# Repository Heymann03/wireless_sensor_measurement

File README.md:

# master research project
## Design and Realization of Wireless Measurement System for Resistive Sensors
### Objectives
1. Measuring the resistance of a sensor of any given range from 200K - 6M.
2. Displaying the data through an OLED.
3. Transmitting the acquired data to a remote station.
4. Monitoring the resistance in real-time.
5. Recording the measured data.

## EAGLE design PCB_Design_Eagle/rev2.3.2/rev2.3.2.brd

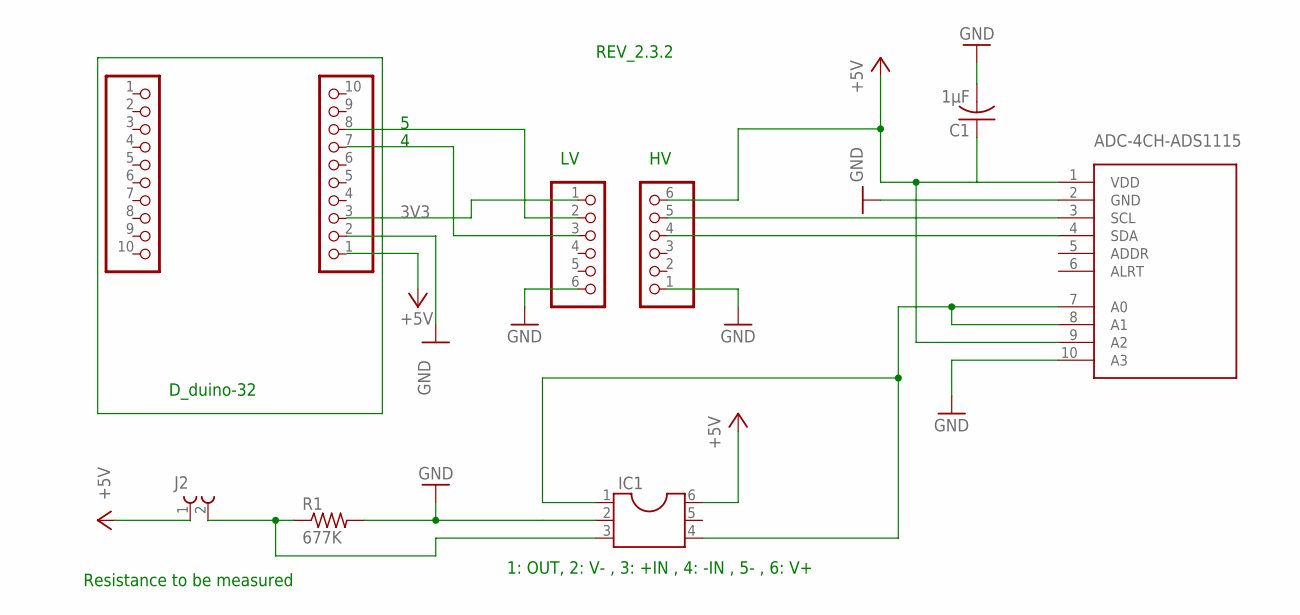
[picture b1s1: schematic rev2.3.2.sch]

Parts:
C1: 1µF; C025-025X050
IC1: DIL6S; SOCKET-06
J2: 691103110002
JP1, JP4: PINHD-1X6; 1X06
JP3, JP5: PINHD-1X10; 1X10
R1: 677K; 0204/5
U$1: ADC-4CH-ADS1115

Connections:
3V3: JP1.1
4: JP1.3
+5V: IC1.6, J2.1
A1: IC1.1, IC1.4, U$1.7 (A0), U$1.8 (A1)
GND: C1.2, IC1.2, JP1.6, JP4.1, JP5.2, R1.2, U$1.2 (GND), U$1.10 (A3)
unnamed: IC1.3, J2.2, R1.1
unnamed: JP1.2, JP5.8
unnamed: JP4.5, U$1.3 (SCL)
unnamed: JP4.4, U$1.4 (SDA)
VDD: C1.1, JP4.6, U$1.9 (A2)

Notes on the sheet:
Resistance to be measured
1: OUT, 2: V- , 3: +IN , 4: -IN , 5- , 6: V+
D_duino-32
REV_2.3.2

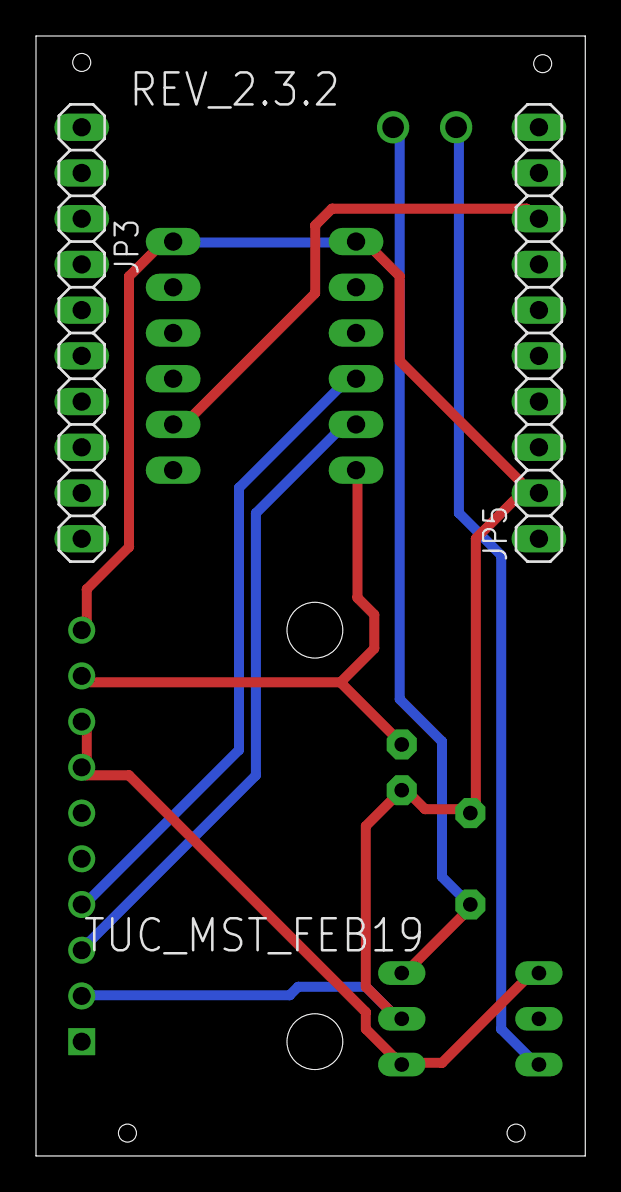
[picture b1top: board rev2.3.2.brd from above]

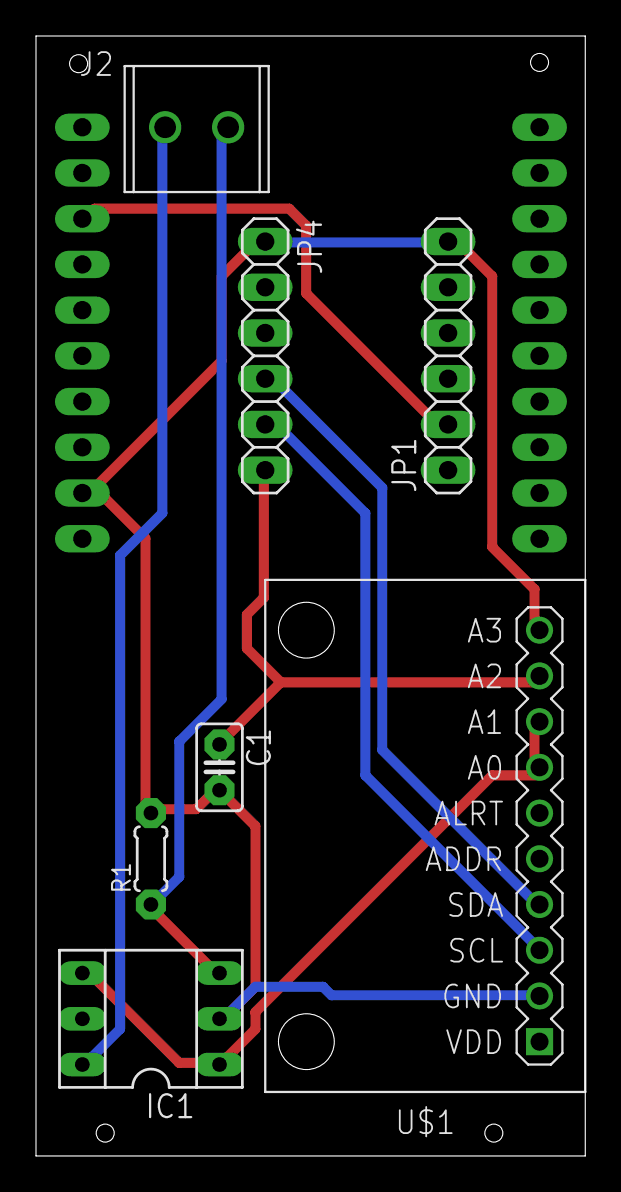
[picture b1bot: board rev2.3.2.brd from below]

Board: 2 copper layers, 30.5 x 62.2 mm, 9 parts (7 on the bottom side), 8 nets.

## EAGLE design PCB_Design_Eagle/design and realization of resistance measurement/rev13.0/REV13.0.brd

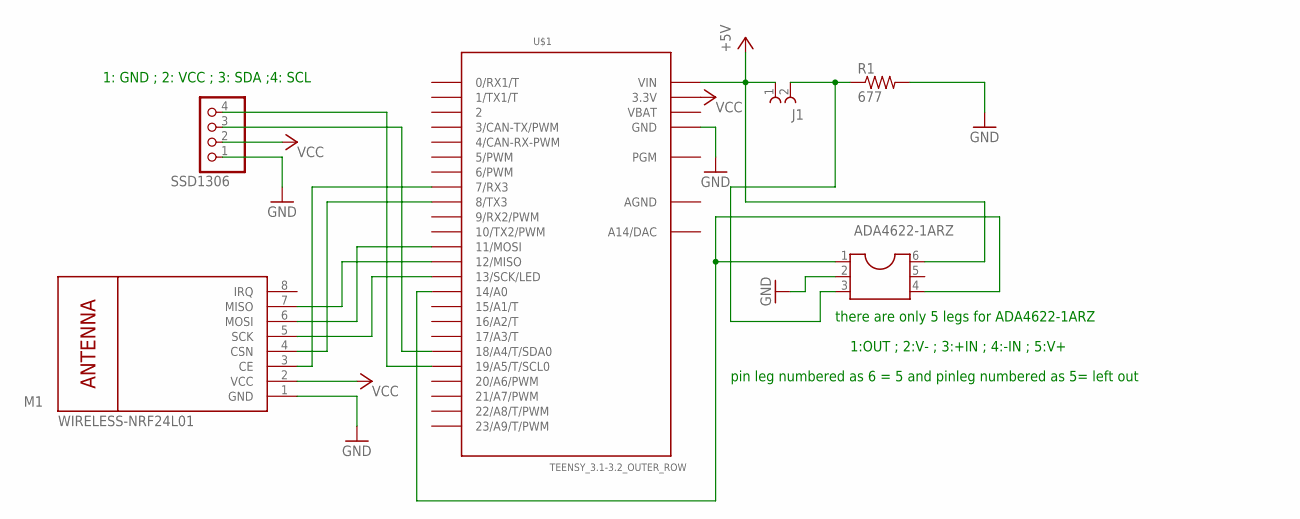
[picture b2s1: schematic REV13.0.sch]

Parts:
ADA4622-1ARZ: DIL6/4; DIL06-4
J1: 691214100002
M1: WIRELESS-NRF24L01
R1: 677; 0204/5
SSD1306: PINHD-1X4; 1X04
U$1: TEENSY_3.1-3.2_OUTER_ROW; TEENSY_3.0-3.2&LC_OUTER_ROW

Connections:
+5V: ADA4622-1ARZ.6, J1.1 (2), U$1.VIN
AGND: U$1.AGND
GND: ADA4622-1ARZ.2, M1.1 (GND), R1.2, SSD1306.1, U$1.GND, U$1.GND1 (GND)
unnamed: ADA4622-1ARZ.3, J1.2 (1), R1.1
unnamed: M1.5 (SCK), U$1.13 (13/SCK/LED)
unnamed: M1.6 (MOSI), U$1.11 (11/MOSI)
unnamed: M1.7 (MISO), U$1.12 (12/MISO)
unnamed: M1.4 (CSN), U$1.8 (8/TX3)
unnamed: M1.3 (CE), U$1.7 (7/RX3)
unnamed: SSD1306.4, U$1.19/A5 (19/A5/T/SCL0)
unnamed: SSD1306.3, U$1.18/A4 (18/A4/T/SDA0)
unnamed: ADA4622-1ARZ.1, ADA4622-1ARZ.4, U$1.14/A0
VBAT: U$1.VBAT
VCC: M1.2 (VCC), SSD1306.2, U$1.3.3V, U$1.3.3V1 (3.3V)

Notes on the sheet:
1: GND ; 2: VCC ; 3: SDA ;4: SCL
1:OUT ; 2:V- ; 3:+IN ; 4:-IN ; 5:V+
pin leg numbered as 6 = 5 and pinleg numbered as 5= left out
there are only 5 legs for ADA4622-1ARZ

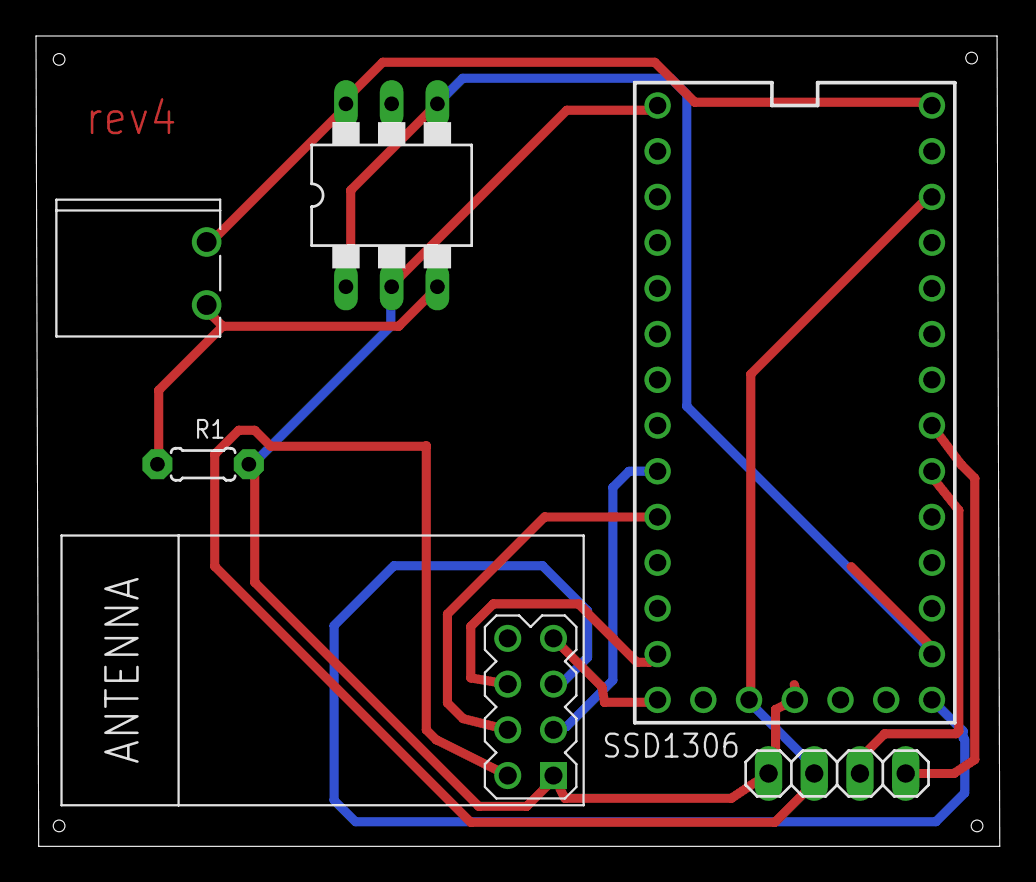
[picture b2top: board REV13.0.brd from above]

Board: 2 copper layers, 53.5 x 45.0 mm, 6 parts (0 on the bottom side), 12 nets.

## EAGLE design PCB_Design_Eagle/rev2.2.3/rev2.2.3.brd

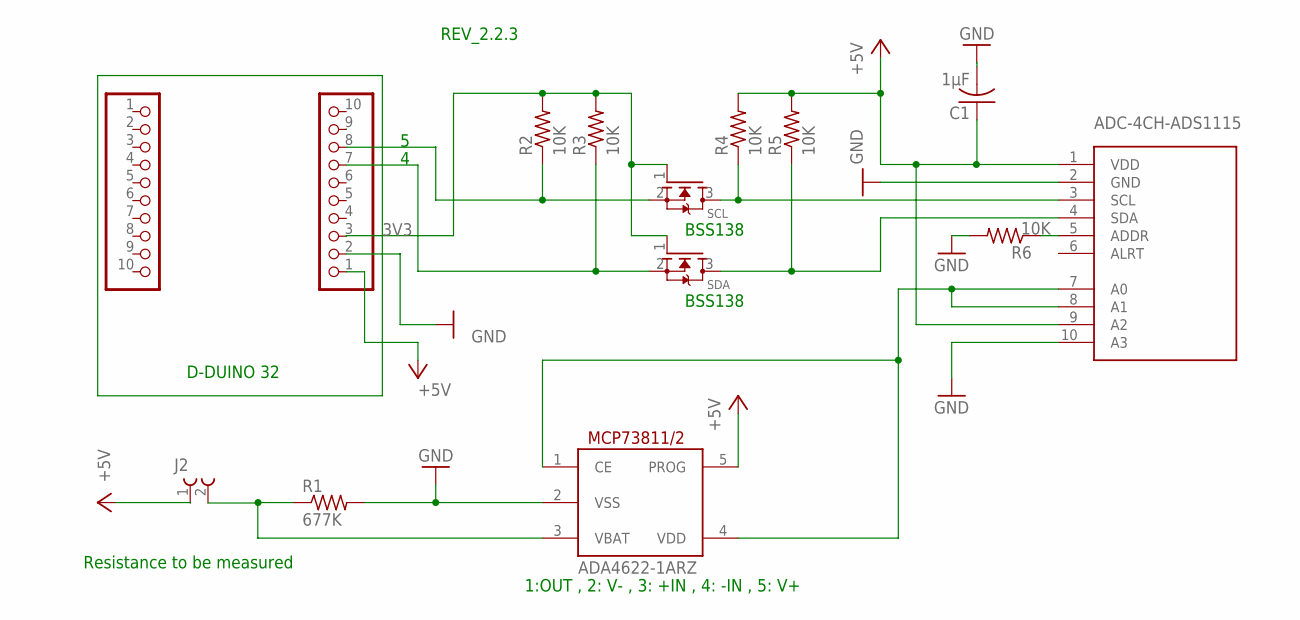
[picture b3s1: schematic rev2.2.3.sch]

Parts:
ADA4622-1ARZ: MCP73811/2; SOT23-5L
C1: 1µF; C1608
J2: 691103110002
JP1, JP3: PINHD-1X10; 1X10
R1: 677K; M0805
R2, R3, R4, R5, R6: 10K; M0805
SCL: MOSFET-NWAVE; SOT23-W
SDA: MOSFET-NWAVE; SOT23-W
U$1: ADC-4CH-ADS1115

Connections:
3V3: JP1.3, R2.2, R3.2, SCL.1 (G), SDA.1 (G)
4: JP1.7, R3.1, SDA.2 (S)
+5V: ADA4622-1ARZ.5 (PROG), J2.1, JP1.1
A1: ADA4622-1ARZ.1 (CE), ADA4622-1ARZ.4 (VDD), U$1.7 (A0), U$1.8 (A1)
GND: ADA4622-1ARZ.2 (VSS), C1.2, JP1.2, R1.2, R6.2, U$1.2 (GND), U$1.10 (A3)
unnamed: ADA4622-1ARZ.3 (VBAT), J2.2, R1.1
unnamed: JP1.8, R2.1, SCL.2 (S)
unnamed: R6.1, U$1.5 (ADDR)
SCL: R4.1, SCL.3 (D), U$1.3 (SCL)
SDA: R5.1, SDA.3 (D), U$1.4 (SDA)
VDD: C1.1, R4.2, R5.2, U$1.1 (VDD), U$1.9 (A2)

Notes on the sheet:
1:OUT , 2: V- , 3: +IN , 4: -IN , 5: V+
Resistance to be measured
BSS138
REV_2.2.3
D-DUINO 32

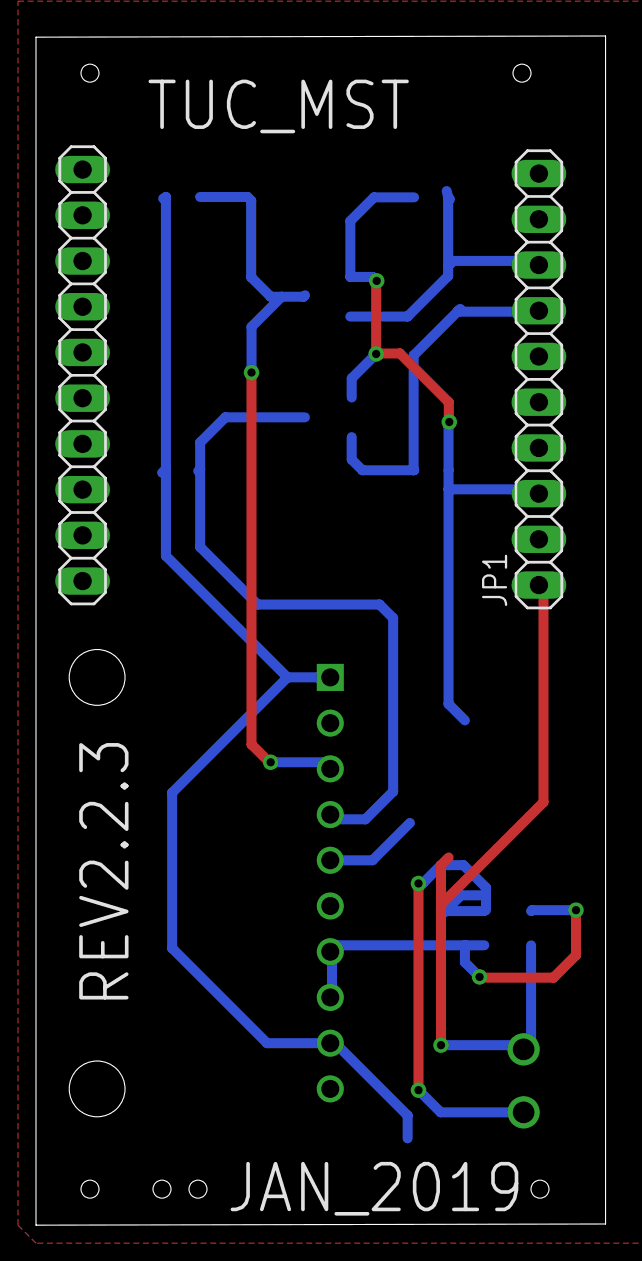
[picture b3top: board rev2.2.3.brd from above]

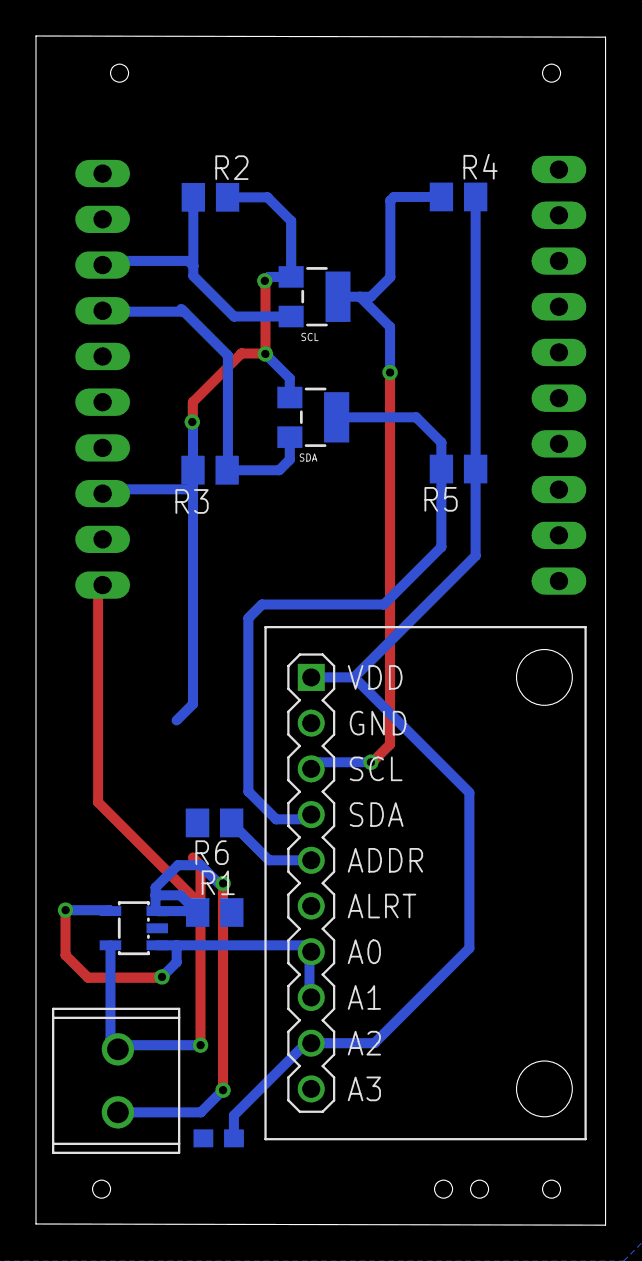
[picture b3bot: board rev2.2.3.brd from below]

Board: 2 copper layers, 31.6 x 66.1 mm, 14 parts (12 on the bottom side), 11 nets.

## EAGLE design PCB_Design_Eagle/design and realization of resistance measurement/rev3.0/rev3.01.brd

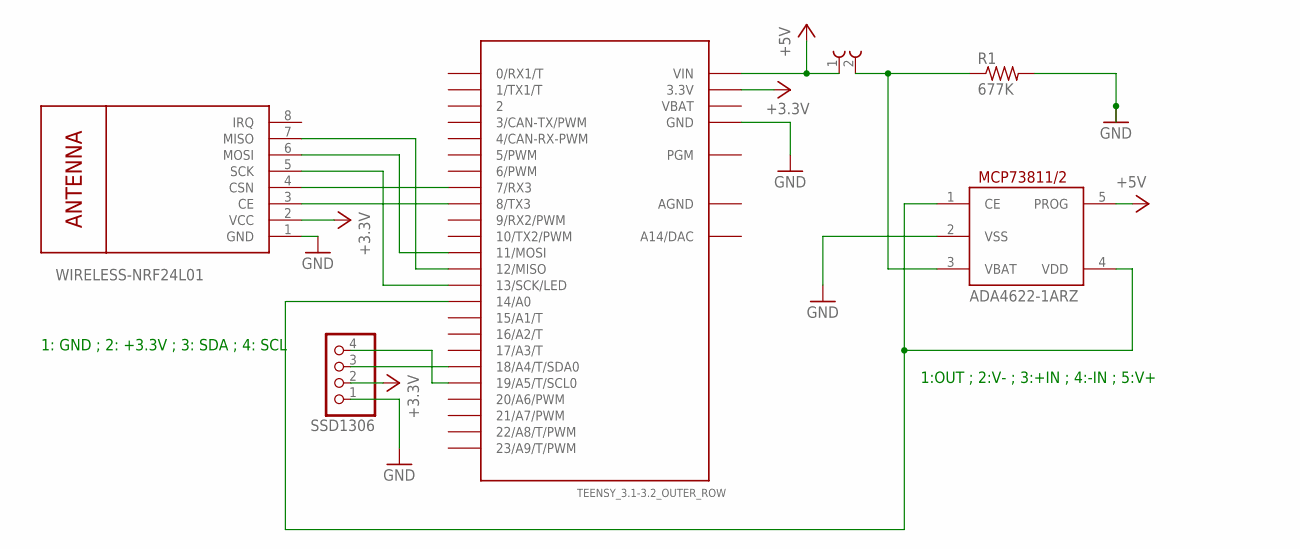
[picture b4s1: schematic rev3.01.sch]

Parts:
ADA4622-1ARZ: MCP73811/2; SOT23-5L
M1: WIRELESS-NRF24L01
R1: 677K; R0805W
R_MES: 691214310002
SSD1306: PINHD-1X4; 1X04
U$2: TEENSY_3.1-3.2_OUTER_ROW; TEENSY_3.0-3.2&LC_OUTER_ROW

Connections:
+5V: ADA4622-1ARZ.5 (PROG), R_MES.1, U$2.VIN
AGND: U$2.AGND
GND: ADA4622-1ARZ.2 (VSS), M1.1 (GND), R1.2, SSD1306.1, U$2.GND, U$2.GND1 (GND)
unnamed: ADA4622-1ARZ.3 (VBAT), R1.1, R_MES.2
unnamed: SSD1306.3, U$2.18/A4 (18/A4/T/SDA0)
unnamed: SSD1306.4, U$2.19/A5 (19/A5/T/SCL0)
unnamed: M1.7 (MISO), U$2.12 (12/MISO)
unnamed: ADA4622-1ARZ.1 (CE), ADA4622-1ARZ.4 (VDD), U$2.14/A0
unnamed: M1.6 (MOSI), U$2.11 (11/MOSI)
unnamed: M1.5 (SCK), U$2.13 (13/SCK/LED)
unnamed: M1.4 (CSN), U$2.7 (7/RX3)
unnamed: M1.3 (CE), U$2.8 (8/TX3)
V+: M1.2 (VCC), SSD1306.2, U$2.3.3V, U$2.3.3V1 (3.3V)
VBAT: U$2.VBAT

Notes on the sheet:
1: GND ; 2: +3.3V ; 3: SDA ; 4: SCL
1:OUT ; 2:V- ; 3:+IN ; 4:-IN ; 5:V+

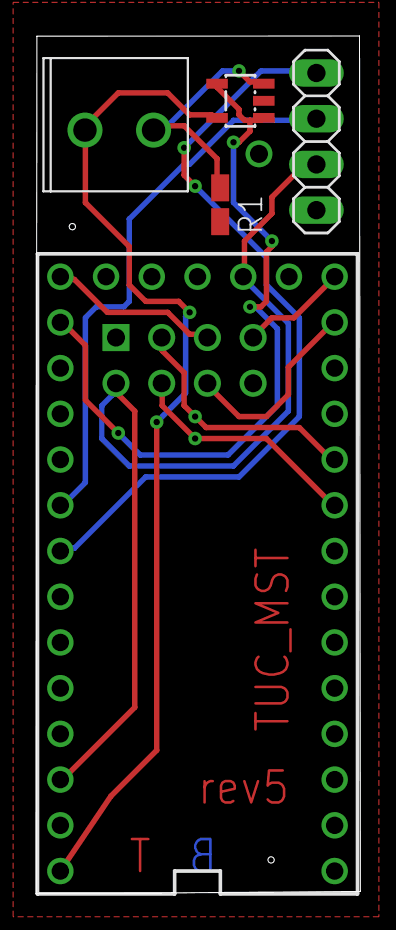
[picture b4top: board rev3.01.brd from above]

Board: 2 copper layers, 18.0 x 47.7 mm, 6 parts (1 on the bottom side), 12 nets.

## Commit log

2018-09-25 Update README.md
    I'm trying to use this code to read resistance value from arduino and transmit using nRF24L01. not working!!!
2020-03-24 local_repo
2020-03-24 project_overview

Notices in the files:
parts and their libraries:
TerminalBlocks: Copyright: Würth Elektronik
diy-modules: Released under the Creative Commons Attribution 4.0 International License: http://creativecommons.org/licenses/by/4.0
